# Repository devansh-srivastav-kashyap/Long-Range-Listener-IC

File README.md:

# Long-Range-Listener-IC
This repository has PCB design of an IC amplifying the far distanced audio.

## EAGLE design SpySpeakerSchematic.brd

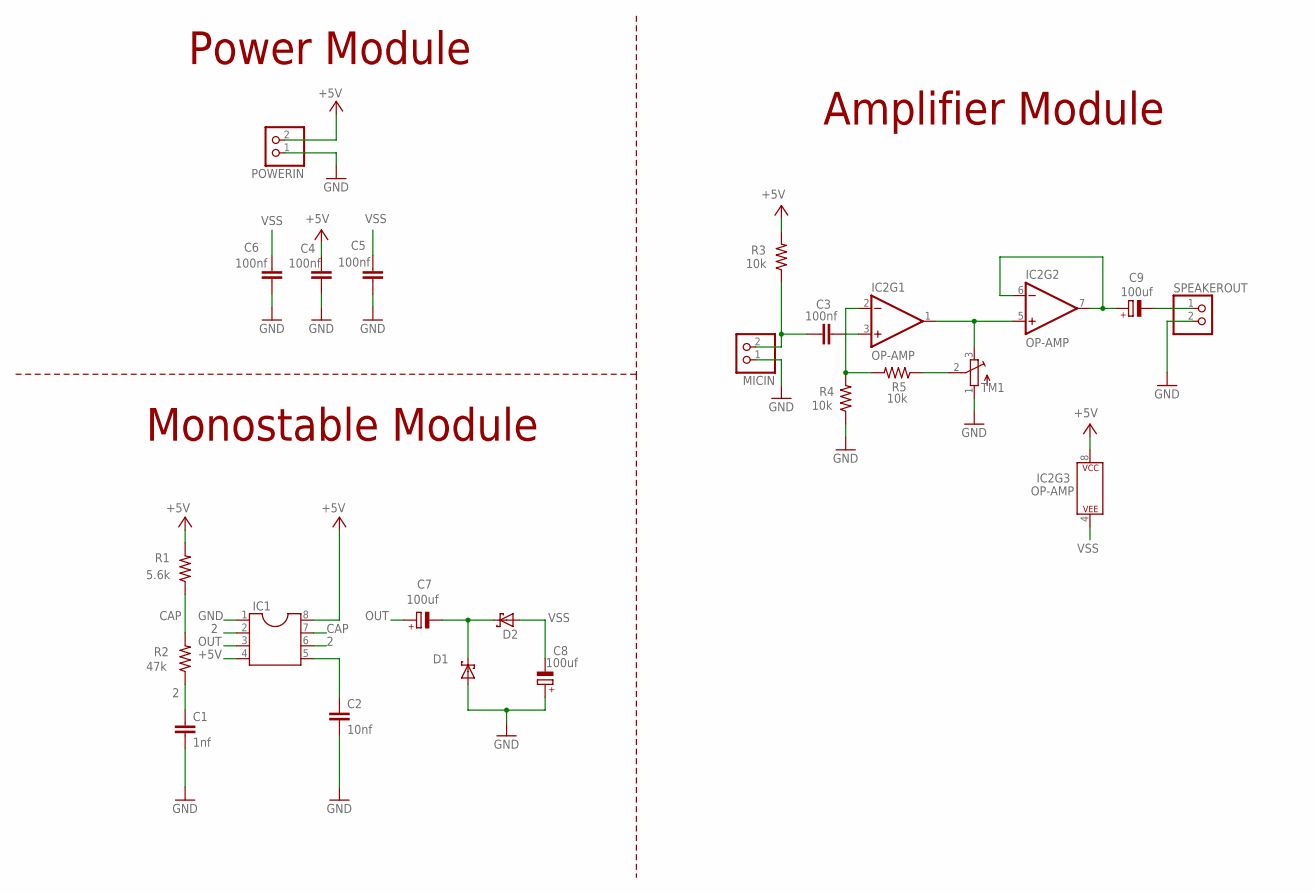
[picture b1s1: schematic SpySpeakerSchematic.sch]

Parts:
C1: 1nf; C025-025X050
C2: 10nf; C025-025X050
C3, C4, C5, C6: 100nf; C025-025X050
C7, C8, C9: 100uf; E2-5
D1, D2: SCHOTTKY-DIODEDO41-7; DO41-7
IC1: DIL8; DIL08
IC2: OP-AMP; DIP08
MICIN: PINHD-1X2; 1X02
POWERIN: PINHD-1X2; 1X02
R1: 5.6k; 0204/5
R2: 47k; 0204/5
R3, R4, R5: 10k; 0204/5
SPEAKEROUT: PINHD-1X2; 1X02
TM1: TRIMPOT3386; TRIM-3386

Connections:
2: C1.1, IC1.2, IC1.6, R2.1
+5V: C4.1, IC1.4, IC1.8, IC2.8 (P$V+), POWERIN.2, R1.2, R3.2
CAP: IC1.7, R1.1, R2.2
GND: C1.2, C2.2, C4.2, C5.2, C6.2, C8.+, D1.A, IC1.1, MICIN.1, POWERIN.1, R4.1, SPEAKEROUT.2, TM1.1 (A)
unnamed: C7.-, D1.C, D2.C
unnamed: C3.1, MICIN.2, R3.1
unnamed: R5.1, TM1.2 (S)
unnamed: C2.1, IC1.5
unnamed: C3.2, IC2.3 (+IN)
unnamed: IC2.1 (OUT), IC2.5 (+IN), TM1.3 (E)
unnamed: IC2.2 (-IN), R4.2, R5.2
unnamed: C9.+, IC2.6 (-IN), IC2.7 (OUT)
unnamed: C9.-, SPEAKEROUT.1
OUT: C7.+, IC1.3
VSS: C5.1, C6.1, C8.-, D2.A, IC2.4 (P$V-)

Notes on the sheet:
Power Module
Monostable Module
Amplifier Module

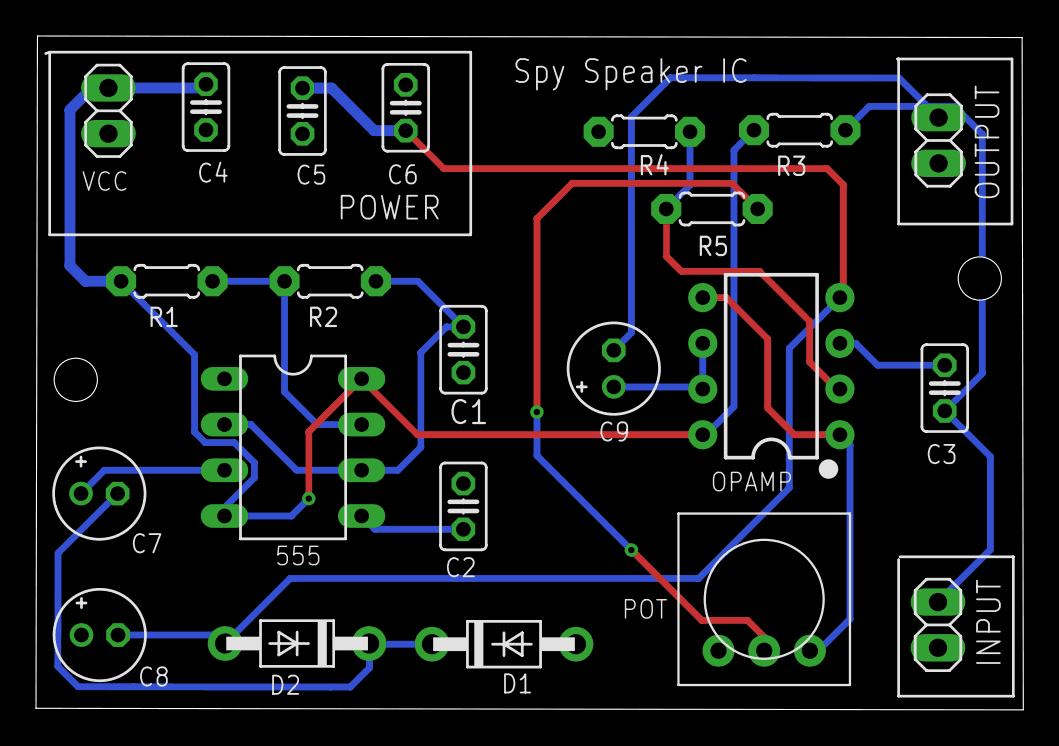
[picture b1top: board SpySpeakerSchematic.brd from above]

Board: 2 copper layers, 54.9 x 37.4 mm, 22 parts (0 on the bottom side), 15 nets.

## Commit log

2021-09-18 Schematic
2021-09-18 Board Layout
2021-09-18 Gerber Files
2021-09-18 Images
2021-09-18 Board IC

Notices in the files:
parts and their libraries:
SparkFun-IC-Amplifiers: Licensing: Creative Commons ShareAlike 4.0 International - https://creativecommons.org/licenses/by-sa/4.0
